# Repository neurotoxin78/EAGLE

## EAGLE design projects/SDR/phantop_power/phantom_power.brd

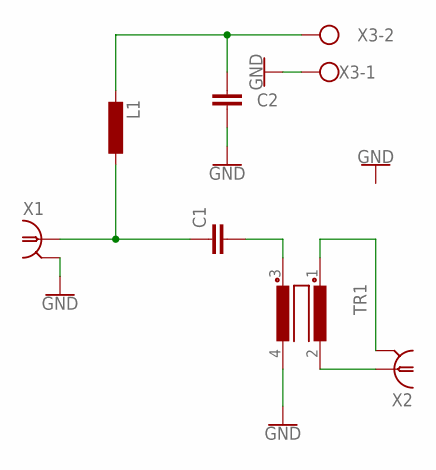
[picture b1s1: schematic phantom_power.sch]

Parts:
C1, C2: C-EUC1206K; C1206K
L1: L-EU6000-XXX-RC; 6000-XXXX-RC
TR1: R1405UB1/2; B1/2
X1, X2: 227161-8; AMP_227161
X3: W237-102

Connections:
GND: C2.2, TR1.4, X1.2, X3.1
unnamed: C1.1, L1.1, X1.1
unnamed: C2.1, L1.2, X3.2
unnamed: C1.2, TR1.3
unnamed: TR1.2, X2.1
unnamed: TR1.1, X2.2

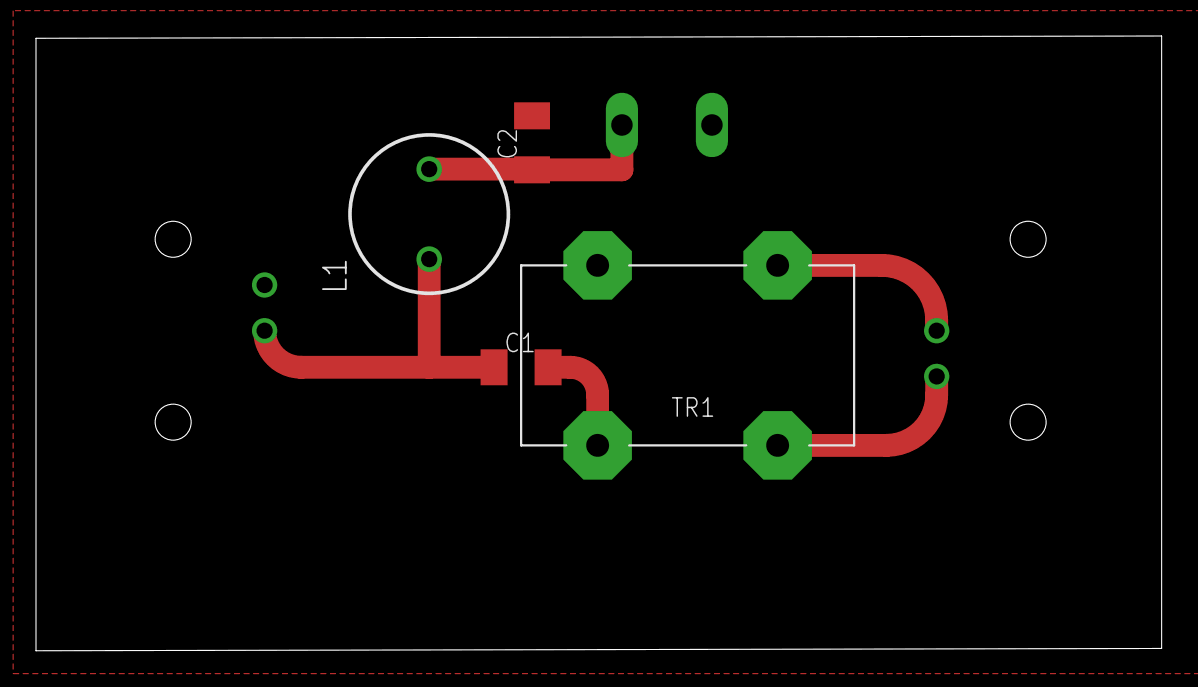
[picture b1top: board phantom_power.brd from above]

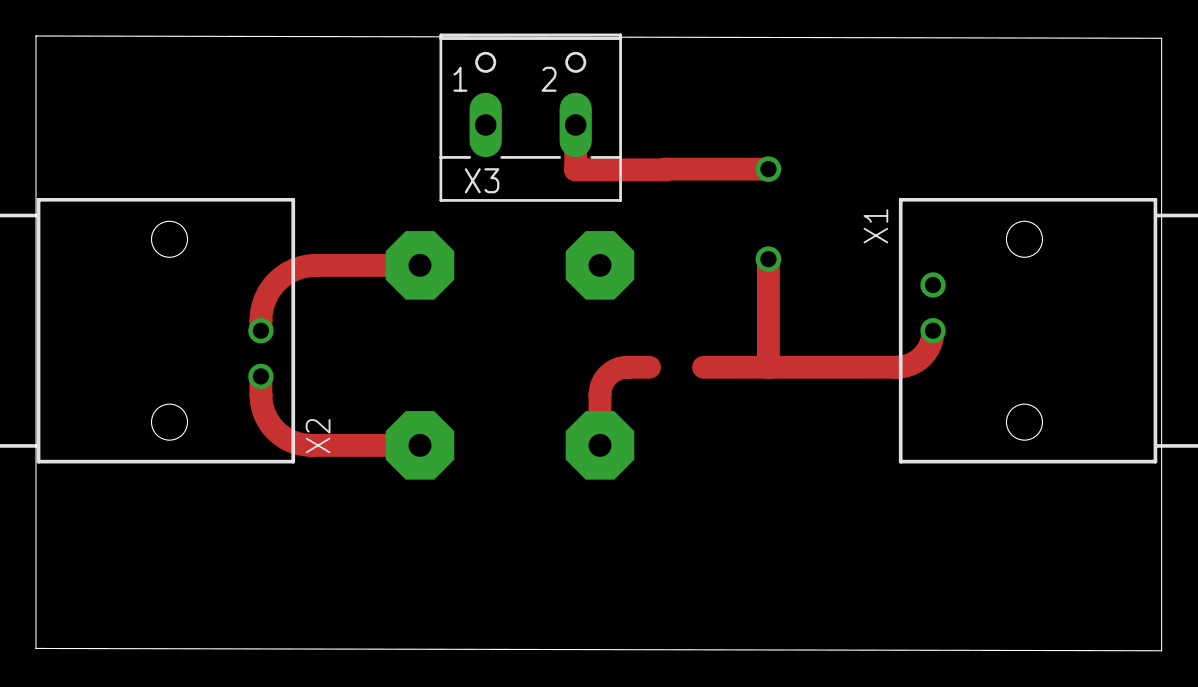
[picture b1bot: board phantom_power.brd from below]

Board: 2 copper layers, 62.5 x 34.2 mm, 7 parts (3 on the bottom side), 6 nets.

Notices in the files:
parts and their libraries:
SparkFun-PowerSymbols: Licensing: Creative Commons ShareAlike 4.0 International - https://creativecommons.org/licenses/by-sa/4.0
